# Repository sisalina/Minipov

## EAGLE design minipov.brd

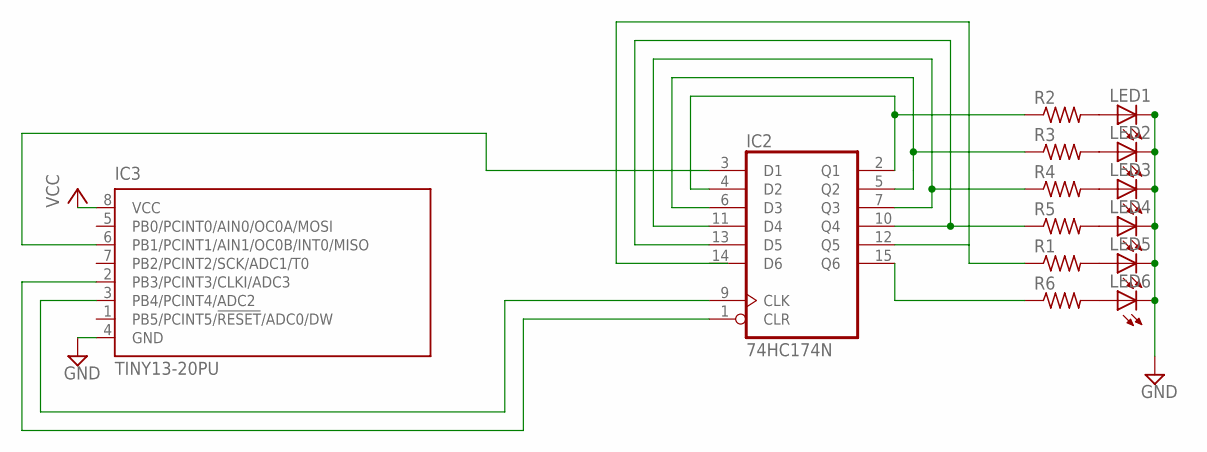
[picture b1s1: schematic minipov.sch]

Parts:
IC2: 74HC174N; DIL16
IC3: TINY13-20PU; DIL08
LED1, LED2, LED3, LED4, LED5, LED6: LED10MM
R1, R2, R3, R4, R5, R6: R-US_0207/5V; 0207/5V

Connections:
GND: IC2.8 (GND), IC3.4 (GND), LED1.K (C), LED2.K (C), LED3.K (C), LED4.K (C), LED5.K (C), LED6.K (C)
unnamed: IC2.1 (CLR), IC3.2 (PB3/PCINT3/CLKI/ADC3)
unnamed: IC2.9 (CLK), IC3.3 (PB4/PCINT4/ADC2)
unnamed: IC2.3 (D1), IC3.6 (PB1/PCINT1/AIN1/OC0B/INT0/MISO)
unnamed: IC2.7 (Q3), IC2.11 (D4), R4.1
unnamed: IC2.10 (Q4), IC2.13 (D5), R5.1
unnamed: IC2.12 (Q5), R1.1
unnamed: IC2.2 (Q1), IC2.4 (D2), R2.1
unnamed: IC2.5 (Q2), IC2.6 (D3), R3.1
unnamed: IC2.15 (Q6), R6.1
unnamed: LED1.A, R2.2
unnamed: LED2.A, R3.2
unnamed: LED3.A, R4.2
unnamed: LED4.A, R5.2
unnamed: LED5.A, R1.2
unnamed: LED6.A, R6.2
VCC: IC2.16 (VCC), IC3.8 (VCC)

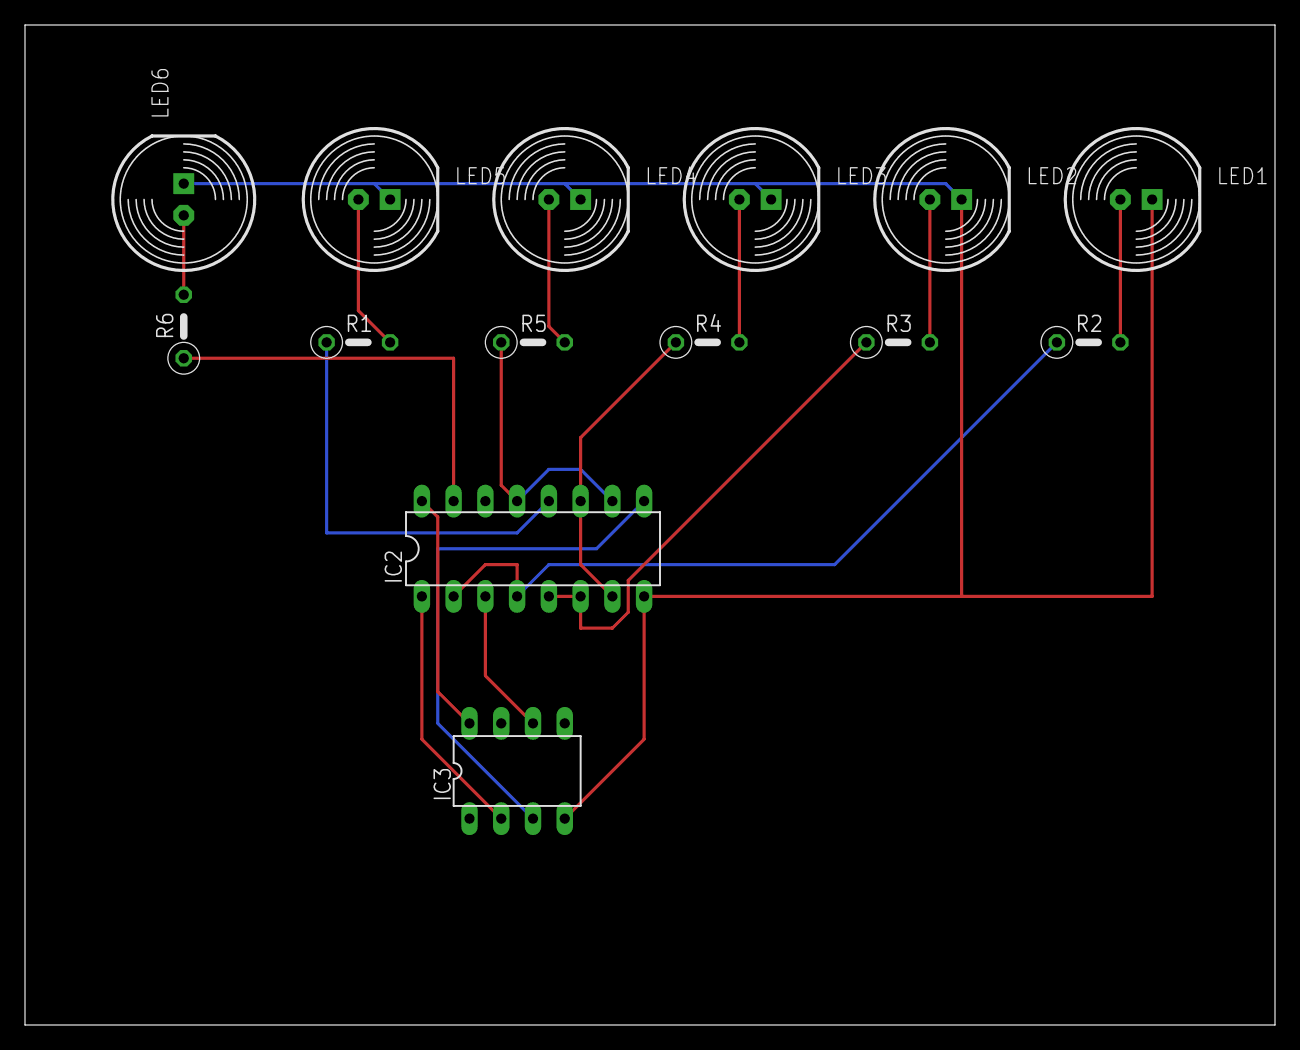
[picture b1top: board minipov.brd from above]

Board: 2 copper layers, 100.0 x 80.0 mm, 14 parts (0 on the bottom side), 17 nets.

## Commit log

2012-03-03 minipov tutorial in 555riente.blogspot.com
2012-03-03 555riente.blogspot.com
